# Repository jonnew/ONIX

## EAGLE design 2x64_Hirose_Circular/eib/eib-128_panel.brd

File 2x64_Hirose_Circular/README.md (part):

<!-- START doctoc generated TOC please keep comment here to allow auto update -->
<!-- DON'T EDIT THIS SECTION, INSTEAD RE-RUN doctoc TO UPDATE -->
**Table of Contents**  *generated with [DocToc](https://github.com/thlorenz/doctoc)*

- [128 channel headstage module for rat tetrode drives](#128-channel-headstage-module-for-rat-tetrode-drives)
  - [Features](#features)
  - [Bill of materials](#bill-of-materials)
  - [TODO](#todo)
  - [Hardware and Documentation Licensing](#hardware-and-documentation-licensing)

<!-- END doctoc generated TOC please keep comment here to allow auto update -->

### 128 channel headstage module for rat tetrode drives
A very low profile digital headstage for amplifying, filtering, and digitizing
microwire voltage data from a microdrive implant. Up to 256 wires (64 tetrodes)
can be acquired.

#### Features
- Circular form factor is aimed at conformation with **tetrode drive** assemblies
 - Low profile, stacked connectorization using 0.4mm pitch [Hirose DF40](http://www.digikey.com/product-search/en?FV=ffec4097) mezzanine headers
- SPI interface options for:
 - 128 channels using a single double data-rate LVDS bus (32 tetrodes)
 - 256 channels using two double data-rate LVDS busses (64 tetrodes)
- Integrated electrode plating and impedance testing

#### Bill of materials
The bill of materials for the headstage, EIBs, spacer boards, and SPI interface
boards can be found on [this google
doc](https://docs.google.com/spreadsheets/d/1F-KWcdvH_63iXjZf0cgCfDiFX6XXW3qw6rlR8DZrFpQ/edit?usp=sharing).

#### TODO
- [ ] For the implants with VTA recordings -- where will these static
  electrodes interface with the EIB. Will they just take an couple 'tetrode
  spots', or is something more specialized needed?
    - Edit: maybe make a special EIB with a connector coming from a flex pcb
      from the VTA implants.
- [ ] In talking to Jakob, I realized that I can share a single CS, MOSI, and
  SCLK bus among all 4 intan chips assuming (1) I don't mind that all the chips
  do the same thing (2) I make sure that the accumulating decrease in the
  effective resistance of having 2X100 ohm resistors close to each other
  (multidrop config) is not going to mess with the LVDS signal integrity.
    - To implement this (in the simplest way possible) I should just be able to
      jumper the CS, MOSI, and SCLK lines at the level of SPI interface board.
      If this works without chaning any of the headstage terminations, then
      great, I just saved 6 wires!
    - Note that this strategy does not require a change to the headstages, just
      the interface board. I will move forward with this idea because it will
      allow me to use the headstages for 128 channel acquisition in the
      meantime.
- [ ] Experiments with the color based tracker indicate that a diffuser,
  preferably something very similar to a tiny ping-pong ball is required on the
  head-direction LEDS on the SPI interface. In general, the SPI interface
  should accommodate whatever solution I come up with. Also, we can get rid of
  the 'wings' on the SPI interface since the geometric tracking idea was
  ill-conceived.
    - [ ] LED choices: Use green and blue for the SPI interface board. The orange
      LED matches the room lighting and is hard to track
- [ ] I need to make sure that he DF40 headers are not going to short onto the
  vias underneath the connectors on the EIB. This should be done empirically.
  - EDIT: they do not short, but there is a different problem: one of the gold
    pins on TT23 of the EIB hits the outer edge of the DF40 receptical above
    it. This pin needs to be moved. More generally, I need to add vertical
    keepouts to the DF40 parts to prevent this in the future.

#### Completed TODOs
- [x] Analog connections terminating at the inputs to an RHD chip do not need
  to feed through to the next board. However, digital connections __always__
  should feed through because they need to make it to the headstage interface
  - Is there a way to prevent stubs in the digital feed troughs that will go
    the wrong way?
- [x] Does it make a difference if the header or the receptacle is next to the
  RHD, specifically in regard to stack height. i.e. is there going to be enough
  room for the potted chip?
  - Selected a connector that has various options for stack height, up to 3mm
    which will be more than enough
- [x] Make sure the circuit has __ample test-points__, especially for probing
  GND, VDD, REF, ELEC_TEST, AUX_OUT.
  - I did my best, but was not able to get the ELEC_TEST pinned out due to
    routing issues. However, these signals have only a standard CMOS analog
    switch between their wire entry point and the RHD chip, so I'm not sure
    test points onboard are super critical.
- [x] Make the annualar ring on test points larger. Its hard to notice how tiny
  everything on these boards are when doing the layout.
- [x] Address Reid's concern about routing high impedance ELEC_TEST lines near
  digital signals
- [x] Add three axis accelerometer to one of the RHD's aux analog inputs
  - Ask for Reid's opinion on the possibility of this chip introducing HF noise
    into the RHD chip sitting right below it.
  - Reid did not think it would be an issue
- [x] Stack height concerns __test empirically using mockups__
 - The ADX is sitting right over an RHD. This leads to an effective stack
   height of their combined thickness. Solution: only populate the to ADX since
   thats all you need anyway. 
 - Just for the record, the ADX is 1.5 mm tall. The potted RHD is 0.8 mm. Total
   stack height = 2.3 + 2.3\*0.1 ~ 2.5 mm. This is a stack height option for
   the hirose connectors, so I think even if this issue arises for some reason,
   I can simply use a taller hirose.
 - The 74HC4053 is a pretty thick chip (standard TSSOP). I got 2 mm stack
   height headers. Will it fit? Its 1.75 mm thick max, so it should fit
   (barely). Also, need to take into account that the bottom headstage is
   rotated 90 deg. relative to the top. It looks like nothing will move
   underneath the 74HC4053 so long as the bottom ADX is not populated, but I
   need to test this on some cheapo boards before making the real ones!
 - Should get stack height of potted die from Reid just to be safe.
  - EDIT: Potted chip is ~0.8 mm tall. 
- [x] Do I really need the four holes in the center of the board. They are
  meant to be fore fiber optics, but they are a serious pain when routing the
  EIBs.
  - EDIT: ended up keeping them and taking the time to route around them
- [x] The EIB needs mounting holes. Maybe something that will fit the old style
  drive bodies with a triangular mounts.
 - Idea: Use a central t-nut on the drive body. This way, there only has to be
   one hole to mount the EIB and the connection will be very strong, especially
   if some sacrificial 'bumps' are placed on the 3D printed pad that will make
   contact with the bottom of the EIB.
 - I created a standard mounting fixture called EIB_MOUNT_A. This provides a
   center hole for a M2 or 2-56 screw and two alignment holes for tabs on the
   drive body's mounting plate.
- [x] The silkscreen on the tetrodes is too small. Make it bigger and move
  toward the inner part of the EIB.
- [x] On the SPI interface, on the mock ups from OSH park, small vias failed to
  support distinctions between octagon style plated holes and round holes. This
  means that my clever way of distinguish SPI interface polarity was a bust. 
- [x] The holes for the spi wire are too small - multiply by 1.5
- [x] The boarder silkscreens on the small passives (0402 and smaller) is too
  close to the pads and is not showing up on the boards.
- [x] Add VDD and GND test points, with large vias, to the periphery of the
  SPI interface board to make for easy testing using a benchtop power supply.
  In fact, do this for all the boards that don't have it already.
- [x] The SPI interface needs to be changed in the following ways.
  - Get rid of fins, they will never work
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
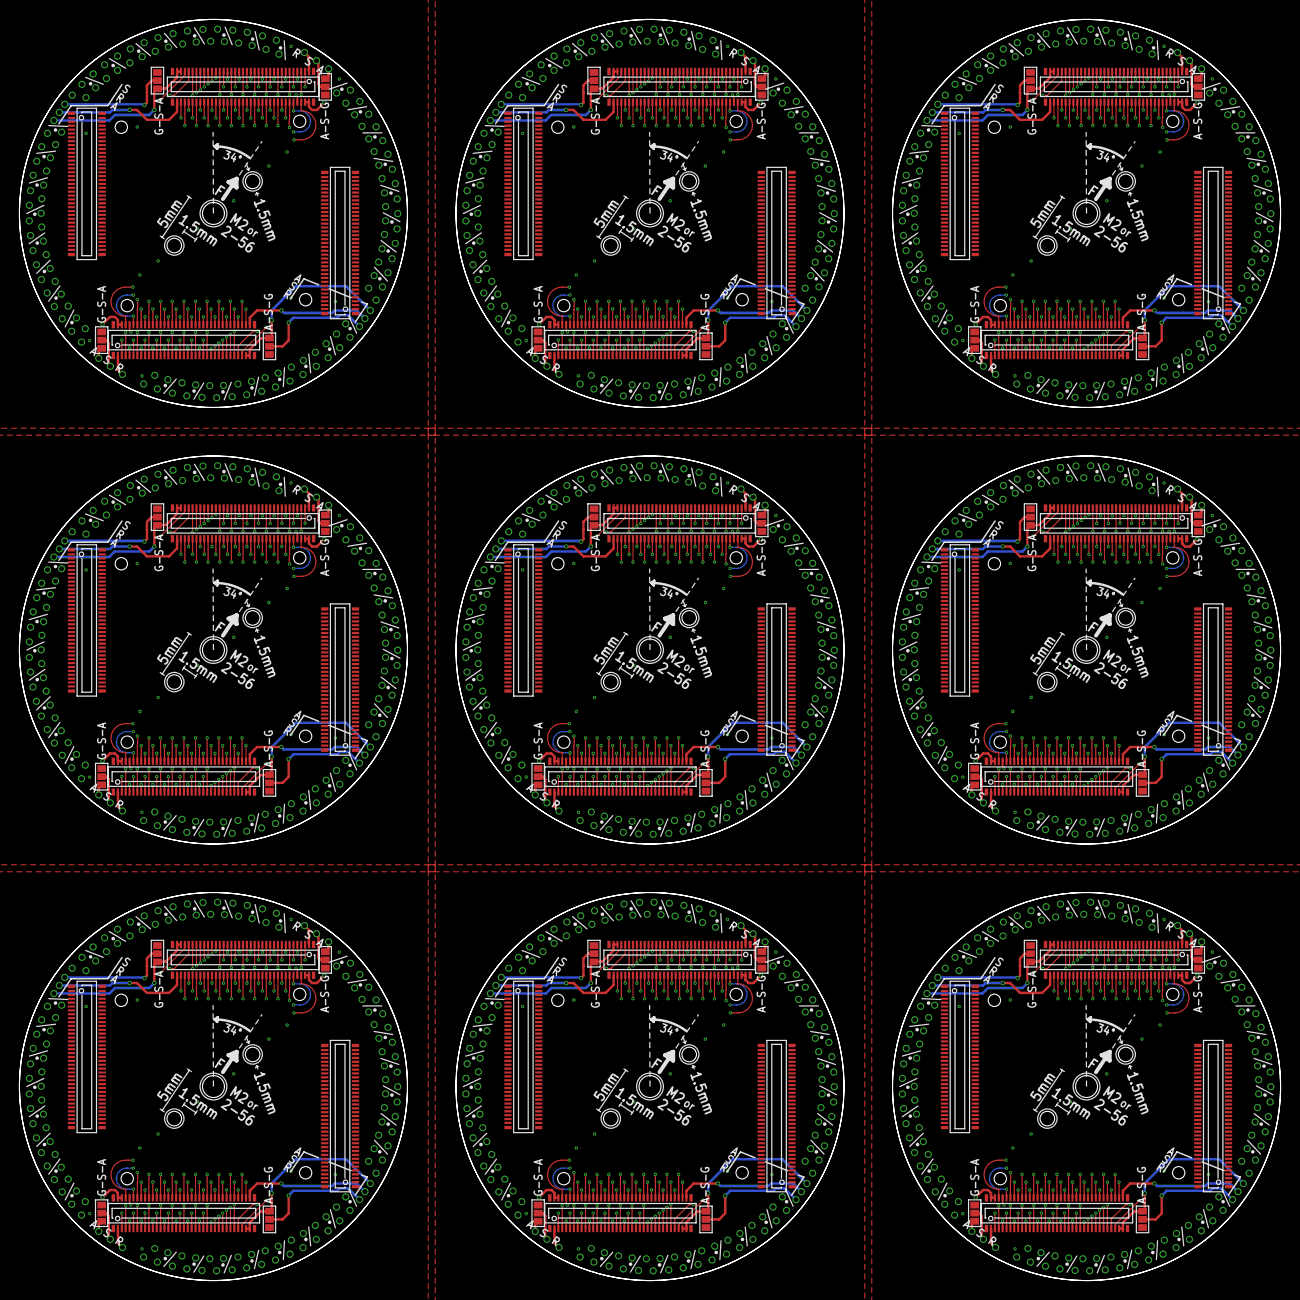
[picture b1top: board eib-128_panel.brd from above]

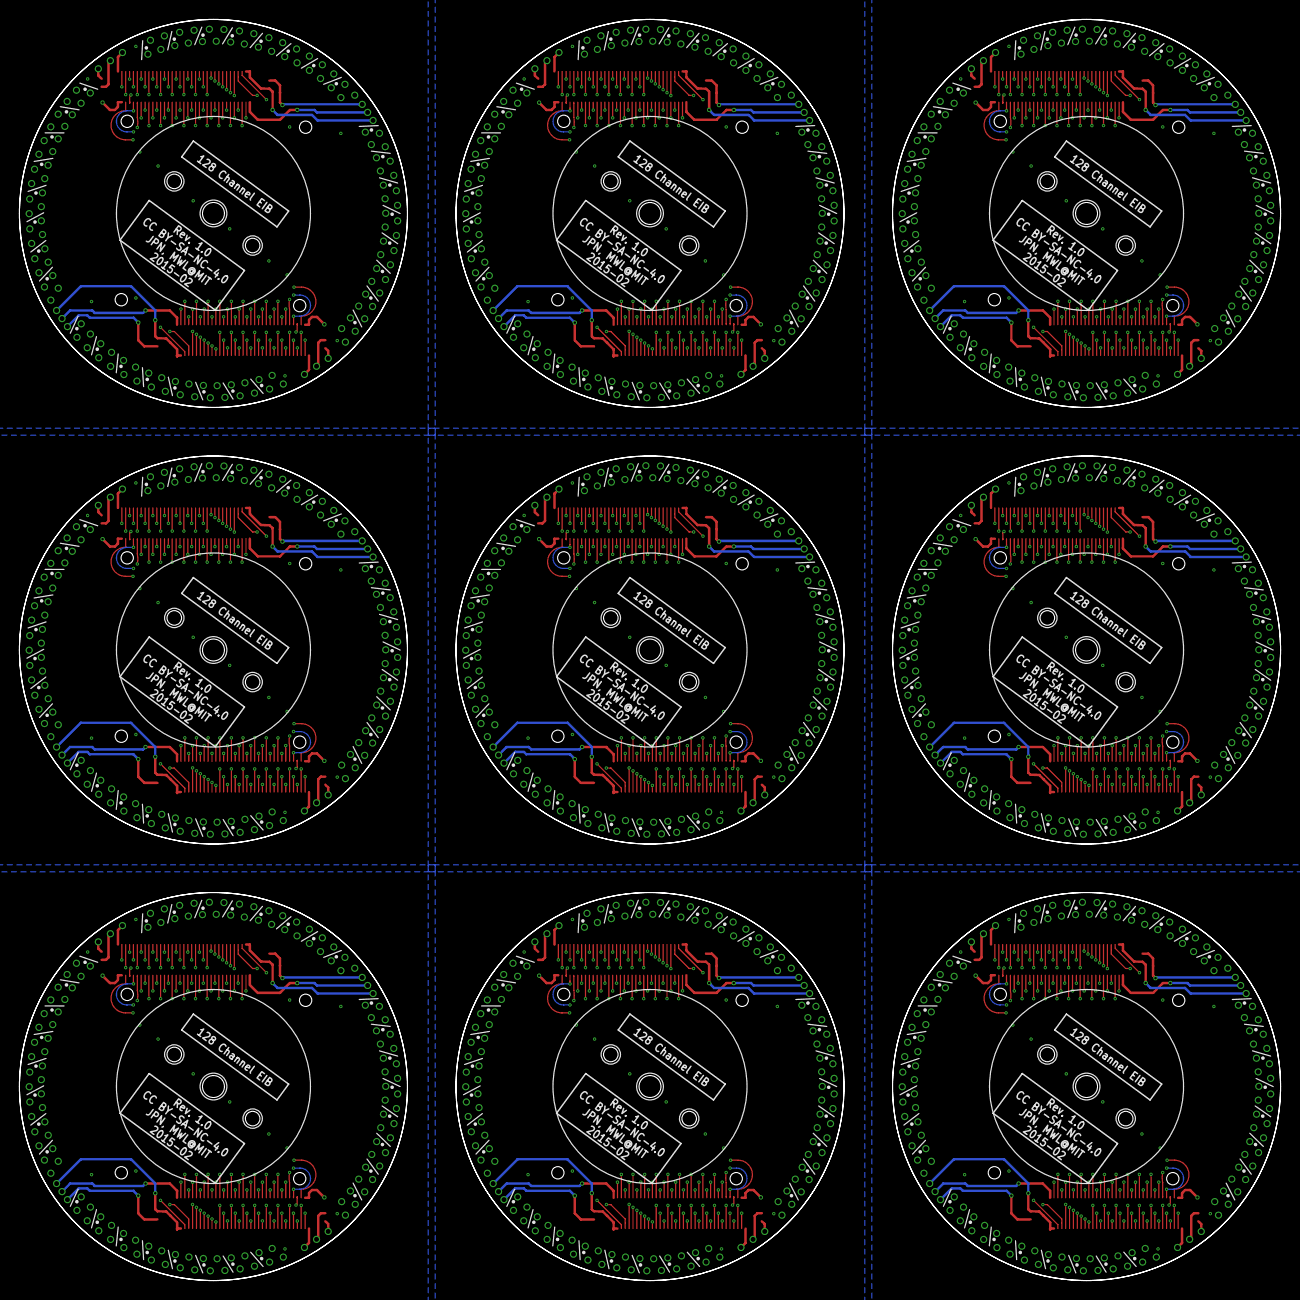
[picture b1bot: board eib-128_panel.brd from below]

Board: 4 copper layers, 130.0 x 130.0 mm, 477 parts (144 on the bottom side), 1269 nets.

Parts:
AGND_A0, AGND_A1, AGND_A2, AGND_A3, AGND_A4, AGND_A5, AGND_A6, AGND_A7, AGND_A8, AGND_A9, AGND_A10, AGND_A11, AGND_A12, AGND_A13, AGND_A14, AGND_A15, AGND_A16, AGND_A17: LRG_GP; GOLDPIN_0.5ID_0.7OD
AGND_B0, AGND_B1, AGND_B2, AGND_B3, AGND_B4, AGND_B5, AGND_B6, AGND_B7, AGND_B8, AGND_B9, AGND_B10, AGND_B11, AGND_B12, AGND_B13, AGND_B14, AGND_B15, AGND_B16, AGND_B17: LRG_GP; GOLDPIN_0.5ID_0.7OD
AIN_N0T, AIN_N0T1, AIN_N0T2, AIN_N0T3, AIN_N0T4, AIN_N0T5, AIN_N0T6, AIN_N0T7, AIN_N0T8: DF40HEAD; DF40-70HEAD-EIB
AIN_S0T, AIN_S0T1, AIN_S0T2, AIN_S0T3, AIN_S0T4, AIN_S0T5, AIN_S0T6, AIN_S0T7, AIN_S0T8: DF40HEAD; DF40-70HEAD-EIB
MECH_E0T, MECH_E0T1, MECH_E0T2, MECH_E0T3, MECH_E0T4, MECH_E0T5, MECH_E0T6, MECH_E0T7, MECH_E0T8: DF40HEAD; DF40-70HEAD
MECH_W0T, MECH_W0T1, MECH_W0T2, MECH_W0T3, MECH_W0T4, MECH_W0T5, MECH_W0T6, MECH_W0T7, MECH_W0T8: DF40HEAD; DF40-70HEAD
REF_A0, REF_A1, REF_A2, REF_A3, REF_A4, REF_A5, REF_A6, REF_A7, REF_A8, REF_A9, REF_A10, REF_A11, REF_A12, REF_A13, REF_A14, REF_A15, REF_A16, REF_A17: LRG_GP; GOLDPIN_0.5ID_0.7OD
REF_B0, REF_B1, REF_B2, REF_B3, REF_B4, REF_B5, REF_B6, REF_B7, REF_B8, REF_B9, REF_B10, REF_B11, REF_B12, REF_B13, REF_B14, REF_B15, REF_B16, REF_B17: LRG_GP; GOLDPIN_0.5ID_0.7OD
SHLD_A0, SHLD_A1, SHLD_A2, SHLD_A3, SHLD_A4, SHLD_A5, SHLD_A6, SHLD_A7, SHLD_A8, SHLD_A9, SHLD_A10, SHLD_A11, SHLD_A12, SHLD_A13, SHLD_A14, SHLD_A15, SHLD_A16, SHLD_A17: LRG_GP; GOLDPIN_0.5ID_0.7OD
SHLD_B0, SHLD_B1, SHLD_B2, SHLD_B3, SHLD_B4, SHLD_B5, SHLD_B6, SHLD_B7, SHLD_B8, SHLD_B9, SHLD_B10, SHLD_B11, SHLD_B12, SHLD_B13, SHLD_B14, SHLD_B15, SHLD_B16, SHLD_B17: LRG_GP; GOLDPIN_0.5ID_0.7OD
SJ_A0, SJ_A1, SJ_A2, SJ_A3, SJ_A4, SJ_A5, SJ_A6, SJ_A7, SJ_A8, SJ_A9, SJ_A10, SJ_A11, SJ_A12, SJ_A13, SJ_A14, SJ_A15, SJ_A16, SJ_A17: SJ_2_0402
SJ_B0, SJ_B1, SJ_B2, SJ_B3, SJ_B4, SJ_B5, SJ_B6, SJ_B7, SJ_B8, SJ_B9, SJ_B10, SJ_B11, SJ_B12, SJ_B13, SJ_B14, SJ_B15, SJ_B16, SJ_B17: SJ_2_0402
TET0, TET32, TET64, TET96, TET128, TET160, TET192, TET224, TET256: 0; TETRODE_128_0.5ID_0.7OD
TET1, TET33, TET65, TET97, TET129, TET161, TET193, TET225, TET257: 1; TETRODE_128_0.5ID_0.7OD
TET2, TET34, TET66, TET98, TET130, TET162, TET194, TET226, TET258: 2; TETRODE_128_0.5ID_0.7OD
TET3, TET35, TET67, TET99, TET131, TET163, TET195, TET227, TET259: 3; TETRODE_128_0.5ID_0.7OD
TET4, TET36, TET68, TET100, TET132, TET164, TET196, TET228, TET260: 4; TETRODE_128_0.5ID_0.7OD
TET5, TET37, TET69, TET101, TET133, TET165, TET197, TET229, TET261: 5; TETRODE_128_0.5ID_0.7OD
TET6, TET38, TET70, TET102, TET134, TET166, TET198, TET230, TET262: 6; TETRODE_128_0.5ID_0.7OD
TET7, TET39, TET71, TET103, TET135, TET167, TET199, TET231, TET263: 7; TETRODE_128_0.5ID_0.7OD
TET8, TET40, TET72, TET104, TET136, TET168, TET200, TET232, TET264: 8; TETRODE_128_0.5ID_0.7OD
TET9, TET41, TET73, TET105, TET137, TET169, TET201, TET233, TET265: 9; TETRODE_128_0.5ID_0.7OD
TET10, TET42, TET74, TET106, TET138, TET170, TET202, TET234, TET266: 10; TETRODE_128_0.5ID_0.7OD
TET11, TET43, TET75, TET107, TET139, TET171, TET203, TET235, TET267: 11; TETRODE_128_0.5ID_0.7OD
TET12, TET44, TET76, TET108, TET140, TET172, TET204, TET236, TET268: 12; TETRODE_128_0.5ID_0.7OD
TET13, TET45, TET77, TET109, TET141, TET173, TET205, TET237, TET269: 13; TETRODE_128_0.5ID_0.7OD
TET14, TET46, TET78, TET110, TET142, TET174, TET206, TET238, TET270: 14; TETRODE_128_0.5ID_0.7OD
TET15, TET47, TET79, TET111, TET143, TET175, TET207, TET239, TET271: 15; TETRODE_128_0.5ID_0.7OD
TET16, TET48, TET80, TET112, TET144, TET176, TET208, TET240, TET272: 16; TETRODE_128_0.5ID_0.7OD
TET17, TET49, TET81, TET113, TET145, TET177, TET209, TET241, TET273: 17; TETRODE_128_0.5ID_0.7OD
TET18, TET50, TET82, TET114, TET146, TET178, TET210, TET242, TET274: 18; TETRODE_128_0.5ID_0.7OD
TET19, TET51, TET83, TET115, TET147, TET179, TET211, TET243, TET275: 19; TETRODE_128_0.5ID_0.7OD
TET20, TET52, TET84, TET116, TET148, TET180, TET212, TET244, TET276: 20; TETRODE_128_0.5ID_0.7OD
TET21, TET53, TET85, TET117, TET149, TET181, TET213, TET245, TET277: 21; TETRODE_128_0.5ID_0.7OD
TET22, TET54, TET86, TET118, TET150, TET182, TET214, TET246, TET278: 22; TETRODE_128_0.5ID_0.7OD
TET23, TET55, TET87, TET119, TET151, TET183, TET215, TET247, TET279: 23; TETRODE_128_0.5ID_0.7OD
TET24, TET56, TET88, TET120, TET152, TET184, TET216, TET248, TET280: 24; TETRODE_128_0.5ID_0.7OD
TET25, TET57, TET89, TET121, TET153, TET185, TET217, TET249, TET281: 25; TETRODE_128_0.5ID_0.7OD
TET26, TET58, TET90, TET122, TET154, TET186, TET218, TET250, TET282: 26; TETRODE_128_0.5ID_0.7OD
TET27, TET59, TET91, TET123, TET155, TET187, TET219, TET251, TET283: 27; TETRODE_128_0.5ID_0.7OD
TET28, TET60, TET92, TET124, TET156, TET188, TET220, TET252, TET284: 28; TETRODE_128_0.5ID_0.7OD
TET29, TET61, TET93, TET125, TET157, TET189, TET221, TET253, TET285: 29; TETRODE_128_0.5ID_0.7OD
TET30, TET62, TET94, TET126, TET158, TET190, TET222, TET254, TET286: 30; TETRODE_128_0.5ID_0.7OD
TET31, TET63, TET95, TET127, TET159, TET191, TET223, TET255, TET287: 31; TETRODE_128_0.5ID_0.7OD
U$1, U$2, U$3, U$4, U$5, U$6, U$7, U$8, U$9: EIB_MOUNT_A

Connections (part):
AGND_A0: AGND_A0.P$1, AIN_N0T.69, AIN_N0T.70, SJ_A0.2
AGND_A1: AGND_A1.P$1, AIN_N0T.34, AIN_N0T.35, SJ_A1.2
AGND_A2: AGND_A3.P$1, AIN_N0T1.69, AIN_N0T1.70, SJ_A2.2
AGND_A3: AGND_A2.P$1, AIN_N0T1.34, AIN_N0T1.35, SJ_A3.2
AGND_A4: AGND_A5.P$1, AIN_N0T2.69, AIN_N0T2.70, SJ_A4.2
AGND_A5: AGND_A4.P$1, AIN_N0T2.34, AIN_N0T2.35, SJ_A5.2
AGND_A6: AGND_A7.P$1, AIN_N0T3.69, AIN_N0T3.70, SJ_A6.2
AGND_A7: AGND_A6.P$1, AIN_N0T3.34, AIN_N0T3.35, SJ_A7.2
AGND_A8: AGND_A9.P$1, AIN_N0T4.69, AIN_N0T4.70, SJ_A8.2
AGND_A9: AGND_A8.P$1, AIN_N0T4.34, AIN_N0T4.35, SJ_A9.2
AGND_A10: AGND_A11.P$1, AIN_N0T5.69, AIN_N0T5.70, SJ_A10.2
AGND_A11: AGND_A10.P$1, AIN_N0T5.34, AIN_N0T5.35, SJ_A11.2
AGND_A12: AGND_A13.P$1, AIN_N0T6.69, AIN_N0T6.70, SJ_A12.2
AGND_A13: AGND_A12.P$1, AIN_N0T6.34, AIN_N0T6.35, SJ_A13.2
AGND_A14: AGND_A15.P$1, AIN_N0T7.69, AIN_N0T7.70, SJ_A14.2
AGND_A15: AGND_A14.P$1, AIN_N0T7.34, AIN_N0T7.35, SJ_A15.2
AGND_A16: AGND_A17.P$1, AIN_N0T8.69, AIN_N0T8.70, SJ_A16.2
AGND_A17: AGND_A16.P$1, AIN_N0T8.34, AIN_N0T8.35, SJ_A17.2
AGND_B0: AGND_B0.P$1, AIN_S0T.69, AIN_S0T.70, SJ_B0.2
AGND_B1: AGND_B1.P$1, AIN_S0T.34, AIN_S0T.35, SJ_B1.2
AGND_B2: AGND_B3.P$1, AIN_S0T1.34, AIN_S0T1.35, SJ_B3.2
AGND_B3: AGND_B2.P$1, AIN_S0T1.69, AIN_S0T1.70, SJ_B2.2
AGND_B4: AGND_B5.P$1, AIN_S0T2.34, AIN_S0T2.35, SJ_B5.2
AGND_B5: AGND_B4.P$1, AIN_S0T2.69, AIN_S0T2.70, SJ_B4.2
AGND_B6: AGND_B7.P$1, AIN_S0T3.34, AIN_S0T3.35, SJ_B7.2
AGND_B7: AGND_B6.P$1, AIN_S0T3.69, AIN_S0T3.70, SJ_B6.2
AGND_B8: AGND_B9.P$1, AIN_S0T4.34, AIN_S0T4.35, SJ_B9.2
AGND_B9: AGND_B8.P$1, AIN_S0T4.69, AIN_S0T4.70, SJ_B8.2
AGND_B10: AGND_B11.P$1, AIN_S0T5.34, AIN_S0T5.35, SJ_B11.2
AGND_B11: AGND_B10.P$1, AIN_S0T5.69, AIN_S0T5.70, SJ_B10.2
AGND_B12: AGND_B13.P$1, AIN_S0T6.34, AIN_S0T6.35, SJ_B13.2
AGND_B13: AGND_B12.P$1, AIN_S0T6.69, AIN_S0T6.70, SJ_B12.2
AGND_B14: AGND_B15.P$1, AIN_S0T7.34, AIN_S0T7.35, SJ_B15.2
AGND_B15: AGND_B14.P$1, AIN_S0T7.69, AIN_S0T7.70, SJ_B14.2
AGND_B16: AGND_B17.P$1, AIN_S0T8.34, AIN_S0T8.35, SJ_B17.2
AGND_B17: AGND_B16.P$1, AIN_S0T8.69, AIN_S0T8.70, SJ_B16.2
GND: SJ_A0.1, SJ_A1.1, SJ_B0.1, SJ_B1.1
GND1: SJ_A2.1, SJ_A3.1, SJ_B2.1, SJ_B3.1
GND2: SJ_A4.1, SJ_A5.1, SJ_B4.1, SJ_B5.1
GND3: SJ_A6.1, SJ_A7.1, SJ_B6.1, SJ_B7.1
GND4: SJ_A8.1, SJ_A9.1, SJ_B8.1, SJ_B9.1
GND5: SJ_A10.1, SJ_A11.1, SJ_B10.1, SJ_B11.1
GND6: SJ_A12.1, SJ_A13.1, SJ_B12.1, SJ_B13.1
GND7: SJ_A14.1, SJ_A15.1, SJ_B14.1, SJ_B15.1
GND8: SJ_A16.1, SJ_A17.1, SJ_B16.1, SJ_B17.1
unnamed: SHLD_A0.P$1, SJ_A0.COM
unnamed: SHLD_A1.P$1, SJ_A1.COM
unnamed: SHLD_B0.P$1, SJ_B0.COM
unnamed: SHLD_B1.P$1, SJ_B1.COM
unnamed: AIN_N0T1.33, TET39.3
unnamed: AIN_N0T1.32, TET39.2
unnamed: AIN_N0T1.31, AIN_N0T1.P31, TET39.1
unnamed: AIN_N0T1.30, AIN_N0T1.P30, TET39.0
unnamed: AIN_N0T1.29, AIN_N0T1.P29, TET38.3
unnamed: AIN_N0T1.28, AIN_N0T1.P28, TET38.2
unnamed: AIN_N0T1.27, AIN_N0T1.P27, TET38.1
unnamed: AIN_N0T1.26, AIN_N0T1.P26, TET38.0
unnamed: AIN_N0T1.25, AIN_N0T1.P25, TET37.3
unnamed: AIN_N0T1.24, AIN_N0T1.P24, TET37.2
unnamed: AIN_N0T1.23, AIN_N0T1.P23, TET37.1
unnamed: AIN_N0T1.22, AIN_N0T1.P22, TET37.0
unnamed: AIN_N0T1.21, AIN_N0T1.P21, TET36.3
unnamed: AIN_N0T1.20, AIN_N0T1.P20, TET36.2
unnamed: AIN_N0T1.19, AIN_N0T1.P19, TET36.1
unnamed: AIN_N0T1.18, AIN_N0T1.P18, TET36.0
unnamed: AIN_N0T1.17, AIN_N0T1.P17, TET35.3
unnamed: AIN_N0T1.16, AIN_N0T1.P16, TET35.2
unnamed: AIN_N0T1.15, AIN_N0T1.P15, TET35.1
unnamed: AIN_N0T1.14, AIN_N0T1.P14, TET35.0
unnamed: AIN_N0T1.13, AIN_N0T1.P13, TET34.3
unnamed: AIN_N0T1.12, AIN_N0T1.P12, TET34.2
unnamed: AIN_N0T1.11, AIN_N0T1.P11, TET34.1
unnamed: AIN_N0T1.10, AIN_N0T1.P10, TET34.0
unnamed: AIN_N0T1.9, AIN_N0T1.P9, TET33.3
unnamed: AIN_N0T1.8, AIN_N0T1.P8, TET33.2
unnamed: AIN_N0T1.7, AIN_N0T1.P7, TET33.1
unnamed: AIN_N0T1.6, AIN_N0T1.P6, TET33.0
unnamed: AIN_N0T1.5, AIN_N0T1.P5, TET32.3
unnamed: AIN_N0T1.4, AIN_N0T1.P4, TET32.2
unnamed: AIN_N0T1.3, AIN_N0T1.P3, TET32.1
unnamed: AIN_N0T1.38, AIN_N0T1.P38, TET40.1
unnamed: AIN_N0T1.39, AIN_N0T1.P39, TET40.2
unnamed: AIN_N0T1.40, AIN_N0T1.P40, TET40.3
unnamed: AIN_N0T1.41, AIN_N0T1.P41, TET41.0
unnamed: AIN_N0T1.42, AIN_N0T1.P42, TET41.1
unnamed: AIN_N0T1.43, AIN_N0T1.P43, TET41.2
unnamed: AIN_N0T1.44, AIN_N0T1.P44, TET41.3
unnamed: AIN_N0T1.45, AIN_N0T1.P45, TET42.0
unnamed: AIN_N0T1.46, AIN_N0T1.P46, TET42.1
unnamed: AIN_N0T1.47, AIN_N0T1.P47, TET42.2
unnamed: AIN_N0T1.48, AIN_N0T1.P48, TET42.3
unnamed: AIN_N0T1.49, AIN_N0T1.P49, TET43.0
unnamed: AIN_N0T1.50, AIN_N0T1.P50, TET43.1
unnamed: AIN_N0T1.51, AIN_N0T1.P51, TET43.2
unnamed: AIN_N0T1.52, AIN_N0T1.P52, TET43.3
unnamed: AIN_N0T1.53, AIN_N0T1.P53, TET44.0
unnamed: AIN_N0T1.54, AIN_N0T1.P54, TET44.1
unnamed: AIN_N0T1.55, AIN_N0T1.P55, TET44.2
unnamed: AIN_N0T1.56, AIN_N0T1.P56, TET44.3
unnamed: AIN_N0T1.57, AIN_N0T1.P57, TET45.0
unnamed: AIN_N0T1.58, AIN_N0T1.P58, TET45.1
unnamed: AIN_N0T1.59, AIN_N0T1.P59, TET45.2
unnamed: AIN_N0T1.60, AIN_N0T1.P60, TET45.3
unnamed: AIN_N0T1.61, AIN_N0T1.P61, TET46.0
unnamed: AIN_N0T1.62, AIN_N0T1.P62, TET46.1
unnamed: AIN_N0T1.63, AIN_N0T1.P63, TET46.2
unnamed: AIN_N0T1.64, AIN_N0T1.P64, TET46.3
unnamed: AIN_N0T1.65, TET47.0
unnamed: AIN_N0T1.66, TET47.1
unnamed: AIN_S0T.33, TET23.0
unnamed: AIN_S0T.32, TET23.1
unnamed: AIN_S0T.31, AIN_S0T.P31, TET23.2
unnamed: AIN_S0T.30, AIN_S0T.P30, TET23.3
unnamed: AIN_S0T.29, AIN_S0T.P29, TET22.0
unnamed: AIN_S0T.28, AIN_S0T.P28, TET22.1
unnamed: AIN_S0T.27, AIN_S0T.P27, TET22.2
unnamed: AIN_S0T.26, AIN_S0T.P26, TET22.3
unnamed: AIN_S0T.25, AIN_S0T.P25, TET21.0
unnamed: AIN_S0T.24, AIN_S0T.P24, TET21.1
unnamed: AIN_S0T.23, AIN_S0T.P23, TET21.2
unnamed: AIN_S0T.22, AIN_S0T.P22, TET21.3
unnamed: AIN_S0T.21, AIN_S0T.P21, TET20.0
unnamed: AIN_S0T.20, AIN_S0T.P20, TET20.1
unnamed: AIN_S0T.19, AIN_S0T.P19, TET20.2
unnamed: AIN_S0T.18, AIN_S0T.P18, TET20.3
unnamed: AIN_S0T.17, AIN_S0T.P17, TET19.0
unnamed: AIN_S0T.16, AIN_S0T.P16, TET19.1
unnamed: AIN_S0T.15, AIN_S0T.P15, TET19.2
unnamed: AIN_S0T.14, AIN_S0T.P14, TET19.3
unnamed: AIN_S0T.13, AIN_S0T.P13, TET18.0
unnamed: AIN_S0T.12, AIN_S0T.P12, TET18.1
unnamed: AIN_S0T.11, AIN_S0T.P11, TET18.2
unnamed: AIN_S0T.10, AIN_S0T.P10, TET18.3
unnamed: AIN_S0T.9, AIN_S0T.P9, TET17.0
unnamed: AIN_S0T.8, AIN_S0T.P8, TET17.1
unnamed: AIN_S0T.7, AIN_S0T.P7, TET17.2
unnamed: AIN_S0T.6, AIN_S0T.P6, TET17.3
unnamed: AIN_S0T.5, AIN_S0T.P5, TET16.0
unnamed: AIN_S0T.4, AIN_S0T.P4, TET16.1
unnamed: AIN_S0T.3, AIN_S0T.P3, TET16.2
unnamed: AIN_S0T.38, AIN_S0T.P38, TET24.2
unnamed: AIN_S0T.39, AIN_S0T.P39, TET24.1
unnamed: AIN_S0T.40, AIN_S0T.P40, TET24.0
unnamed: AIN_S0T.41, AIN_S0T.P41, TET25.3
unnamed: AIN_S0T.42, AIN_S0T.P42, TET25.2
unnamed: AIN_S0T.43, AIN_S0T.P43, TET25.1
unnamed: AIN_S0T.44, AIN_S0T.P44, TET25.0
unnamed: AIN_S0T.45, AIN_S0T.P45, TET26.3
unnamed: AIN_S0T.46, AIN_S0T.P46, TET26.2
unnamed: AIN_S0T.47, AIN_S0T.P47, TET26.1
unnamed: AIN_S0T.48, AIN_S0T.P48, TET26.0
unnamed: AIN_S0T.49, AIN_S0T.P49, TET27.3
unnamed: AIN_S0T.50, AIN_S0T.P50, TET27.2
unnamed: AIN_S0T.51, AIN_S0T.P51, TET27.1
unnamed: AIN_S0T.52, AIN_S0T.P52, TET27.0
unnamed: AIN_S0T.53, AIN_S0T.P53, TET28.3
unnamed: AIN_S0T.54, AIN_S0T.P54, TET28.2
unnamed: AIN_S0T.55, AIN_S0T.P55, TET28.1
unnamed: AIN_S0T.56, AIN_S0T.P56, TET28.0
unnamed: AIN_S0T.57, AIN_S0T.P57, TET29.3
unnamed: AIN_S0T.58, AIN_S0T.P58, TET29.2
unnamed: AIN_S0T.59, AIN_S0T.P59, TET29.1
unnamed: AIN_S0T.60, AIN_S0T.P60, TET29.0
unnamed: AIN_S0T.61, AIN_S0T.P61, TET30.3
unnamed: AIN_S0T.62, AIN_S0T.P62, TET30.2
unnamed: AIN_S0T.63, AIN_S0T.P63, TET30.1
unnamed: AIN_S0T.64, AIN_S0T.P64, TET30.0
unnamed: AIN_S0T.65, TET31.3
unnamed: AIN_S0T.66, TET31.2
unnamed: AIN_S0T.67, TET31.1
unnamed: AIN_S0T.68, TET31.0
unnamed: AIN_S0T.2, AIN_S0T.P2, TET16.3
unnamed: AIN_S0T.37, AIN_S0T.P37, TET24.3
unnamed: AIN_N0T1.67, TET47.2
unnamed: AIN_N0T1.68, TET47.3
unnamed: AIN_N0T1.2, AIN_N0T1.P2, TET32.0
unnamed: AIN_N0T1.37, AIN_N0T1.P37, TET40.0
unnamed: AIN_S0T1.33, TET55.0
unnamed: AIN_S0T1.32, TET55.1
unnamed: AIN_S0T1.31, AIN_S0T1.P31, TET55.2
unnamed: AIN_S0T1.30, AIN_S0T1.P30, TET55.3
unnamed: AIN_S0T1.29, AIN_S0T1.P29, TET54.0
unnamed: AIN_S0T1.28, AIN_S0T1.P28, TET54.1
unnamed: AIN_S0T1.27, AIN_S0T1.P27, TET54.2
unnamed: AIN_S0T1.26, AIN_S0T1.P26, TET54.3
unnamed: AIN_S0T1.25, AIN_S0T1.P25, TET53.0
unnamed: AIN_S0T1.24, AIN_S0T1.P24, TET53.1
unnamed: AIN_S0T1.23, AIN_S0T1.P23, TET53.2
unnamed: AIN_S0T1.22, AIN_S0T1.P22, TET53.3
unnamed: AIN_S0T1.21, AIN_S0T1.P21, TET52.0
unnamed: AIN_S0T1.20, AIN_S0T1.P20, TET52.1
unnamed: AIN_S0T1.19, AIN_S0T1.P19, TET52.2
unnamed: AIN_S0T1.18, AIN_S0T1.P18, TET52.3
unnamed: AIN_S0T1.17, AIN_S0T1.P17, TET51.0
unnamed: AIN_S0T1.16, AIN_S0T1.P16, TET51.1
unnamed: AIN_S0T1.15, AIN_S0T1.P15, TET51.2
unnamed: AIN_S0T1.14, AIN_S0T1.P14, TET51.3
unnamed: AIN_S0T1.13, AIN_S0T1.P13, TET50.0
unnamed: AIN_S0T1.12, AIN_S0T1.P12, TET50.1
unnamed: AIN_S0T1.11, AIN_S0T1.P11, TET50.2
unnamed: AIN_S0T1.10, AIN_S0T1.P10, TET50.3
unnamed: AIN_S0T1.9, AIN_S0T1.P9, TET49.0
unnamed: AIN_S0T1.8, AIN_S0T1.P8, TET49.1
unnamed: AIN_S0T1.7, AIN_S0T1.P7, TET49.2
unnamed: AIN_S0T1.6, AIN_S0T1.P6, TET49.3
unnamed: AIN_S0T1.5, AIN_S0T1.P5, TET48.0
unnamed: AIN_S0T1.4, AIN_S0T1.P4, TET48.1
unnamed: AIN_S0T1.3, AIN_S0T1.P3, TET48.2
unnamed: AIN_S0T1.38, AIN_S0T1.P38, TET56.2
unnamed: AIN_S0T1.39, AIN_S0T1.P39, TET56.1
unnamed: AIN_S0T1.40, AIN_S0T1.P40, TET56.0
unnamed: AIN_S0T1.41, AIN_S0T1.P41, TET57.3
unnamed: AIN_S0T1.42, AIN_S0T1.P42, TET57.2
unnamed: AIN_S0T1.43, AIN_S0T1.P43, TET57.1
unnamed: AIN_S0T1.44, AIN_S0T1.P44, TET57.0
unnamed: AIN_S0T1.45, AIN_S0T1.P45, TET58.3
unnamed: AIN_S0T1.46, AIN_S0T1.P46, TET58.2
unnamed: AIN_S0T1.47, AIN_S0T1.P47, TET58.1
unnamed: AIN_S0T1.48, AIN_S0T1.P48, TET58.0
unnamed: AIN_S0T1.49, AIN_S0T1.P49, TET59.3
unnamed: AIN_S0T1.50, AIN_S0T1.P50, TET59.2
unnamed: AIN_S0T1.51, AIN_S0T1.P51, TET59.1
unnamed: AIN_S0T1.52, AIN_S0T1.P52, TET59.0
unnamed: AIN_S0T1.53, AIN_S0T1.P53, TET60.3
unnamed: AIN_S0T1.54, AIN_S0T1.P54, TET60.2
unnamed: AIN_S0T1.55, AIN_S0T1.P55, TET60.1
unnamed: AIN_S0T1.56, AIN_S0T1.P56, TET60.0
unnamed: AIN_S0T1.57, AIN_S0T1.P57, TET61.3
unnamed: AIN_S0T1.58, AIN_S0T1.P58, TET61.2
unnamed: AIN_S0T1.59, AIN_S0T1.P59, TET61.1
unnamed: AIN_S0T1.60, AIN_S0T1.P60, TET61.0
unnamed: AIN_S0T1.61, AIN_S0T1.P61, TET62.3
unnamed: AIN_S0T1.62, AIN_S0T1.P62, TET62.2
unnamed: AIN_S0T1.63, AIN_S0T1.P63, TET62.1
unnamed: AIN_S0T1.64, AIN_S0T1.P64, TET62.0
unnamed: AIN_S0T1.65, TET63.3
unnamed: AIN_S0T1.66, TET63.2
unnamed: AIN_S0T1.67, TET63.1
unnamed: AIN_S0T1.68, TET63.0
unnamed: AIN_S0T1.2, AIN_S0T1.P2, TET48.3
unnamed: AIN_S0T1.37, AIN_S0T1.P37, TET56.3
unnamed: SHLD_A2.P$1, SJ_A2.COM
unnamed: SHLD_A3.P$1, SJ_A3.COM
unnamed: AIN_N0T.33, TET7.3
unnamed: AIN_N0T.32, TET7.2
unnamed: AIN_N0T.31, AIN_N0T.P31, TET7.1
unnamed: AIN_N0T.30, AIN_N0T.P30, TET7.0
unnamed: AIN_N0T.29, AIN_N0T.P29, TET6.3
unnamed: AIN_N0T.28, AIN_N0T.P28, TET6.2
unnamed: AIN_N0T.27, AIN_N0T.P27, TET6.1
unnamed: AIN_N0T.26, AIN_N0T.P26, TET6.0
unnamed: AIN_N0T.25, AIN_N0T.P25, TET5.3
unnamed: AIN_N0T.24, AIN_N0T.P24, TET5.2
unnamed: AIN_N0T.23, AIN_N0T.P23, TET5.1
unnamed: AIN_N0T.22, AIN_N0T.P22, TET5.0
unnamed: AIN_N0T.21, AIN_N0T.P21, TET4.3
unnamed: AIN_N0T.20, AIN_N0T.P20, TET4.2
unnamed: AIN_N0T.19, AIN_N0T.P19, TET4.1
unnamed: AIN_N0T.18, AIN_N0T.P18, TET4.0
unnamed: AIN_N0T.17, AIN_N0T.P17, TET3.3
unnamed: AIN_N0T.16, AIN_N0T.P16, TET3.2
unnamed: AIN_N0T.15, AIN_N0T.P15, TET3.1
unnamed: AIN_N0T.14, AIN_N0T.P14, TET3.0
unnamed: AIN_N0T.13, AIN_N0T.P13, TET2.3
unnamed: AIN_N0T.12, AIN_N0T.P12, TET2.2
unnamed: AIN_N0T.11, AIN_N0T.P11, TET2.1
unnamed: AIN_N0T.10, AIN_N0T.P10, TET2.0
unnamed: AIN_N0T.9, AIN_N0T.P9, TET1.3
unnamed: AIN_N0T.8, AIN_N0T.P8, TET1.2
unnamed: AIN_N0T.7, AIN_N0T.P7, TET1.1
unnamed: AIN_N0T.6, AIN_N0T.P6, TET1.0
unnamed: AIN_N0T.5, AIN_N0T.P5, TET0.3
unnamed: AIN_N0T.4, AIN_N0T.P4, TET0.2
unnamed: AIN_N0T.3, AIN_N0T.P3, TET0.1
unnamed: AIN_N0T.2, AIN_N0T.P2, TET0.0
unnamed: AIN_N0T.38, AIN_N0T.P38, TET8.1
unnamed: AIN_N0T.39, AIN_N0T.P39, TET8.2
unnamed: AIN_N0T.40, AIN_N0T.P40, TET8.3
unnamed: AIN_N0T.41, AIN_N0T.P41, TET9.0
unnamed: AIN_N0T.42, AIN_N0T.P42, TET9.1
unnamed: AIN_N0T.43, AIN_N0T.P43, TET9.2
unnamed: AIN_N0T.44, AIN_N0T.P44, TET9.3
unnamed: AIN_N0T.45, AIN_N0T.P45, TET10.0
unnamed: AIN_N0T.46, AIN_N0T.P46, TET10.1
unnamed: AIN_N0T.47, AIN_N0T.P47, TET10.2
unnamed: AIN_N0T.48, AIN_N0T.P48, TET10.3
unnamed: AIN_N0T.49, AIN_N0T.P49, TET11.0
unnamed: AIN_N0T.50, AIN_N0T.P50, TET11.1
unnamed: AIN_N0T.51, AIN_N0T.P51, TET11.2
unnamed: AIN_N0T.52, AIN_N0T.P52, TET11.3
unnamed: AIN_N0T.53, AIN_N0T.P53, TET12.0
unnamed: AIN_N0T.54, AIN_N0T.P54, TET12.1
unnamed: AIN_N0T.55, AIN_N0T.P55, TET12.2
unnamed: AIN_N0T.56, AIN_N0T.P56, TET12.3
unnamed: AIN_N0T.57, AIN_N0T.P57, TET13.0
unnamed: AIN_N0T.58, AIN_N0T.P58, TET13.1
unnamed: AIN_N0T.59, AIN_N0T.P59, TET13.2
unnamed: AIN_N0T.60, AIN_N0T.P60, TET13.3
unnamed: AIN_N0T.61, AIN_N0T.P61, TET14.0
unnamed: AIN_N0T.62, AIN_N0T.P62, TET14.1
unnamed: AIN_N0T.63, AIN_N0T.P63, TET14.2
unnamed: AIN_N0T.64, AIN_N0T.P64, TET14.3
unnamed: AIN_N0T.65, TET15.0
unnamed: AIN_N0T.66, TET15.1
unnamed: AIN_N0T.67, TET15.2
unnamed: AIN_N0T.68, TET15.3
unnamed: SHLD_B2.P$1, SJ_B2.COM
unnamed: SHLD_B3.P$1, SJ_B3.COM
unnamed: AIN_N0T2.33, TET71.3
unnamed: AIN_N0T2.32, TET71.2
unnamed: AIN_N0T2.31, AIN_N0T2.P31, TET71.1
unnamed: AIN_N0T2.30, AIN_N0T2.P30, TET71.0
unnamed: AIN_N0T2.29, AIN_N0T2.P29, TET70.3
unnamed: AIN_N0T2.28, AIN_N0T2.P28, TET70.2
unnamed: AIN_N0T2.27, AIN_N0T2.P27, TET70.1
unnamed: AIN_N0T2.26, AIN_N0T2.P26, TET70.0
unnamed: AIN_N0T2.25, AIN_N0T2.P25, TET69.3
unnamed: AIN_N0T2.24, AIN_N0T2.P24, TET69.2
unnamed: AIN_N0T2.23, AIN_N0T2.P23, TET69.1
unnamed: AIN_N0T2.22, AIN_N0T2.P22, TET69.0
unnamed: AIN_N0T2.21, AIN_N0T2.P21, TET68.3
unnamed: AIN_N0T2.20, AIN_N0T2.P20, TET68.2
unnamed: AIN_N0T2.19, AIN_N0T2.P19, TET68.1
unnamed: AIN_N0T2.18, AIN_N0T2.P18, TET68.0
unnamed: AIN_N0T2.17, AIN_N0T2.P17, TET67.3
unnamed: AIN_N0T2.16, AIN_N0T2.P16, TET67.2
unnamed: AIN_N0T2.15, AIN_N0T2.P15, TET67.1
unnamed: AIN_N0T2.14, AIN_N0T2.P14, TET67.0
unnamed: AIN_N0T2.13, AIN_N0T2.P13, TET66.3
unnamed: AIN_N0T2.12, AIN_N0T2.P12, TET66.2
unnamed: AIN_N0T2.11, AIN_N0T2.P11, TET66.1
unnamed: AIN_N0T2.10, AIN_N0T2.P10, TET66.0
unnamed: AIN_N0T2.9, AIN_N0T2.P9, TET65.3
unnamed: AIN_N0T2.8, AIN_N0T2.P8, TET65.2
unnamed: AIN_N0T2.7, AIN_N0T2.P7, TET65.1
unnamed: AIN_N0T2.6, AIN_N0T2.P6, TET65.0
unnamed: AIN_N0T2.5, AIN_N0T2.P5, TET64.3
unnamed: AIN_N0T2.4, AIN_N0T2.P4, TET64.2
unnamed: AIN_N0T2.3, AIN_N0T2.P3, TET64.1
unnamed: AIN_N0T2.38, AIN_N0T2.P38, TET72.1
unnamed: AIN_N0T2.39, AIN_N0T2.P39, TET72.2
unnamed: AIN_N0T2.40, AIN_N0T2.P40, TET72.3
unnamed: AIN_N0T2.41, AIN_N0T2.P41, TET73.0
unnamed: AIN_N0T2.42, AIN_N0T2.P42, TET73.1
unnamed: AIN_N0T2.43, AIN_N0T2.P43, TET73.2
unnamed: AIN_N0T2.44, AIN_N0T2.P44, TET73.3
unnamed: AIN_N0T2.45, AIN_N0T2.P45, TET74.0
unnamed: AIN_N0T2.46, AIN_N0T2.P46, TET74.1
unnamed: AIN_N0T2.47, AIN_N0T2.P47, TET74.2
unnamed: AIN_N0T2.48, AIN_N0T2.P48, TET74.3
unnamed: AIN_N0T2.49, AIN_N0T2.P49, TET75.0
unnamed: AIN_N0T2.50, AIN_N0T2.P50, TET75.1
unnamed: AIN_N0T2.51, AIN_N0T2.P51, TET75.2
unnamed: AIN_N0T2.52, AIN_N0T2.P52, TET75.3
unnamed: AIN_N0T2.53, AIN_N0T2.P53, TET76.0
unnamed: AIN_N0T2.54, AIN_N0T2.P54, TET76.1
unnamed: AIN_N0T2.55, AIN_N0T2.P55, TET76.2
unnamed: AIN_N0T2.56, AIN_N0T2.P56, TET76.3
unnamed: AIN_N0T2.57, AIN_N0T2.P57, TET77.0
unnamed: AIN_N0T2.58, AIN_N0T2.P58, TET77.1
unnamed: AIN_N0T2.59, AIN_N0T2.P59, TET77.2
unnamed: AIN_N0T2.60, AIN_N0T2.P60, TET77.3
unnamed: AIN_N0T2.61, AIN_N0T2.P61, TET78.0
unnamed: AIN_N0T2.62, AIN_N0T2.P62, TET78.1
unnamed: AIN_N0T2.63, AIN_N0T2.P63, TET78.2
unnamed: AIN_N0T2.64, AIN_N0T2.P64, TET78.3
unnamed: AIN_N0T2.65, TET79.0
unnamed: AIN_N0T2.66, TET79.1
unnamed: AIN_N0T2.67, TET79.2
unnamed: AIN_N0T2.68, TET79.3
unnamed: AIN_N0T2.2, AIN_N0T2.P2, TET64.0
unnamed: AIN_N0T2.37, AIN_N0T2.P37, TET72.0
unnamed: AIN_S0T2.33, TET87.0
unnamed: AIN_S0T2.32, TET87.1
unnamed: AIN_S0T2.31, AIN_S0T2.P31, TET87.2
unnamed: AIN_S0T2.30, AIN_S0T2.P30, TET87.3
unnamed: AIN_S0T2.29, AIN_S0T2.P29, TET86.0
unnamed: AIN_S0T2.28, AIN_S0T2.P28, TET86.1
unnamed: AIN_S0T2.27, AIN_S0T2.P27, TET86.2
unnamed: AIN_S0T2.26, AIN_S0T2.P26, TET86.3
unnamed: AIN_S0T2.25, AIN_S0T2.P25, TET85.0
unnamed: AIN_S0T2.24, AIN_S0T2.P24, TET85.1
unnamed: AIN_S0T2.23, AIN_S0T2.P23, TET85.2
unnamed: AIN_S0T2.22, AIN_S0T2.P22, TET85.3
unnamed: AIN_S0T2.21, AIN_S0T2.P21, TET84.0
unnamed: AIN_S0T2.20, AIN_S0T2.P20, TET84.1
unnamed: AIN_S0T2.19, AIN_S0T2.P19, TET84.2
unnamed: AIN_S0T2.18, AIN_S0T2.P18, TET84.3
unnamed: AIN_S0T2.17, AIN_S0T2.P17, TET83.0
unnamed: AIN_S0T2.16, AIN_S0T2.P16, TET83.1
unnamed: AIN_S0T2.15, AIN_S0T2.P15, TET83.2
unnamed: AIN_S0T2.14, AIN_S0T2.P14, TET83.3
unnamed: AIN_S0T2.13, AIN_S0T2.P13, TET82.0
unnamed: AIN_S0T2.12, AIN_S0T2.P12, TET82.1
unnamed: AIN_S0T2.11, AIN_S0T2.P11, TET82.2
unnamed: AIN_S0T2.10, AIN_S0T2.P10, TET82.3
unnamed: AIN_S0T2.9, AIN_S0T2.P9, TET81.0
unnamed: AIN_S0T2.8, AIN_S0T2.P8, TET81.1
unnamed: AIN_S0T2.7, AIN_S0T2.P7, TET81.2
unnamed: AIN_S0T2.6, AIN_S0T2.P6, TET81.3
unnamed: AIN_S0T2.5, AIN_S0T2.P5, TET80.0
unnamed: AIN_S0T2.4, AIN_S0T2.P4, TET80.1
unnamed: AIN_S0T2.3, AIN_S0T2.P3, TET80.2
unnamed: AIN_S0T2.38, AIN_S0T2.P38, TET88.2
unnamed: AIN_S0T2.39, AIN_S0T2.P39, TET88.1
unnamed: AIN_S0T2.40, AIN_S0T2.P40, TET88.0
unnamed: AIN_S0T2.41, AIN_S0T2.P41, TET89.3
unnamed: AIN_S0T2.42, AIN_S0T2.P42, TET89.2
unnamed: AIN_S0T2.43, AIN_S0T2.P43, TET89.1
unnamed: AIN_S0T2.44, AIN_S0T2.P44, TET89.0
unnamed: AIN_S0T2.45, AIN_S0T2.P45, TET90.3
unnamed: AIN_S0T2.46, AIN_S0T2.P46, TET90.2
unnamed: AIN_S0T2.47, AIN_S0T2.P47, TET90.1
unnamed: AIN_S0T2.48, AIN_S0T2.P48, TET90.0
unnamed: AIN_S0T2.49, AIN_S0T2.P49, TET91.3
unnamed: AIN_S0T2.50, AIN_S0T2.P50, TET91.2
unnamed: AIN_S0T2.51, AIN_S0T2.P51, TET91.1
unnamed: AIN_S0T2.52, AIN_S0T2.P52, TET91.0
unnamed: AIN_S0T2.53, AIN_S0T2.P53, TET92.3
unnamed: AIN_S0T2.54, AIN_S0T2.P54, TET92.2
unnamed: AIN_S0T2.55, AIN_S0T2.P55, TET92.1
unnamed: AIN_S0T2.56, AIN_S0T2.P56, TET92.0
unnamed: AIN_S0T2.57, AIN_S0T2.P57, TET93.3
unnamed: AIN_S0T2.58, AIN_S0T2.P58, TET93.2
unnamed: AIN_S0T2.59, AIN_S0T2.P59, TET93.1
unnamed: AIN_S0T2.60, AIN_S0T2.P60, TET93.0
unnamed: AIN_S0T2.61, AIN_S0T2.P61, TET94.3
unnamed: AIN_S0T2.62, AIN_S0T2.P62, TET94.2
unnamed: AIN_S0T2.63, AIN_S0T2.P63, TET94.1
unnamed: AIN_S0T2.64, AIN_S0T2.P64, TET94.0
unnamed: AIN_S0T2.65, TET95.3
unnamed: AIN_S0T2.66, TET95.2
unnamed: AIN_S0T2.67, TET95.1
unnamed: AIN_S0T2.68, TET95.0
unnamed: AIN_S0T2.2, AIN_S0T2.P2, TET80.3
unnamed: AIN_S0T2.37, AIN_S0T2.P37, TET88.3
unnamed: SHLD_A4.P$1, SJ_A4.COM
unnamed: SHLD_A5.P$1, SJ_A5.COM
unnamed: SHLD_B4.P$1, SJ_B4.COM
unnamed: SHLD_B5.P$1, SJ_B5.COM
unnamed: AIN_N0T3.33, TET103.3
unnamed: AIN_N0T3.32, TET103.2
unnamed: AIN_N0T3.31, AIN_N0T3.P31, TET103.1
unnamed: AIN_N0T3.30, AIN_N0T3.P30, TET103.0
unnamed: AIN_N0T3.29, AIN_N0T3.P29, TET102.3
unnamed: AIN_N0T3.28, AIN_N0T3.P28, TET102.2
unnamed: AIN_N0T3.27, AIN_N0T3.P27, TET102.1
unnamed: AIN_N0T3.26, AIN_N0T3.P26, TET102.0
unnamed: AIN_N0T3.25, AIN_N0T3.P25, TET101.3
unnamed: AIN_N0T3.24, AIN_N0T3.P24, TET101.2
unnamed: AIN_N0T3.23, AIN_N0T3.P23, TET101.1
unnamed: AIN_N0T3.22, AIN_N0T3.P22, TET101.0
unnamed: AIN_N0T3.21, AIN_N0T3.P21, TET100.3
unnamed: AIN_N0T3.20, AIN_N0T3.P20, TET100.2
unnamed: AIN_N0T3.19, AIN_N0T3.P19, TET100.1
unnamed: AIN_N0T3.18, AIN_N0T3.P18, TET100.0
unnamed: AIN_N0T3.17, AIN_N0T3.P17, TET99.3
unnamed: AIN_N0T3.16, AIN_N0T3.P16, TET99.2
unnamed: AIN_N0T3.15, AIN_N0T3.P15, TET99.1
unnamed: AIN_N0T3.14, AIN_N0T3.P14, TET99.0
unnamed: AIN_N0T3.13, AIN_N0T3.P13, TET98.3
unnamed: AIN_N0T3.12, AIN_N0T3.P12, TET98.2
unnamed: AIN_N0T3.11, AIN_N0T3.P11, TET98.1
unnamed: AIN_N0T3.10, AIN_N0T3.P10, TET98.0
unnamed: AIN_N0T3.9, AIN_N0T3.P9, TET97.3
unnamed: AIN_N0T3.8, AIN_N0T3.P8, TET97.2
unnamed: AIN_N0T3.7, AIN_N0T3.P7, TET97.1
unnamed: AIN_N0T3.6, AIN_N0T3.P6, TET97.0
unnamed: AIN_N0T3.5, AIN_N0T3.P5, TET96.3
unnamed: AIN_N0T3.4, AIN_N0T3.P4, TET96.2
unnamed: AIN_N0T3.3, AIN_N0T3.P3, TET96.1
unnamed: AIN_N0T3.38, AIN_N0T3.P38, TET104.1
unnamed: AIN_N0T3.39, AIN_N0T3.P39, TET104.2
unnamed: AIN_N0T3.40, AIN_N0T3.P40, TET104.3
unnamed: AIN_N0T3.41, AIN_N0T3.P41, TET105.0
unnamed: AIN_N0T3.42, AIN_N0T3.P42, TET105.1
unnamed: AIN_N0T3.43, AIN_N0T3.P43, TET105.2
unnamed: AIN_N0T3.44, AIN_N0T3.P44, TET105.3
unnamed: AIN_N0T3.45, AIN_N0T3.P45, TET106.0
unnamed: AIN_N0T3.46, AIN_N0T3.P46, TET106.1
unnamed: AIN_N0T3.47, AIN_N0T3.P47, TET106.2
unnamed: AIN_N0T3.48, AIN_N0T3.P48, TET106.3
unnamed: AIN_N0T3.49, AIN_N0T3.P49, TET107.0
unnamed: AIN_N0T3.50, AIN_N0T3.P50, TET107.1
unnamed: AIN_N0T3.51, AIN_N0T3.P51, TET107.2
unnamed: AIN_N0T3.52, AIN_N0T3.P52, TET107.3
unnamed: AIN_N0T3.53, AIN_N0T3.P53, TET108.0
unnamed: AIN_N0T3.54, AIN_N0T3.P54, TET108.1
unnamed: AIN_N0T3.55, AIN_N0T3.P55, TET108.2
unnamed: AIN_N0T3.56, AIN_N0T3.P56, TET108.3
unnamed: AIN_N0T3.57, AIN_N0T3.P57, TET109.0
unnamed: AIN_N0T3.58, AIN_N0T3.P58, TET109.1
unnamed: AIN_N0T3.59, AIN_N0T3.P59, TET109.2
unnamed: AIN_N0T3.60, AIN_N0T3.P60, TET109.3
unnamed: AIN_N0T3.61, AIN_N0T3.P61, TET110.0
unnamed: AIN_N0T3.62, AIN_N0T3.P62, TET110.1
unnamed: AIN_N0T3.63, AIN_N0T3.P63, TET110.2
unnamed: AIN_N0T3.64, AIN_N0T3.P64, TET110.3
unnamed: AIN_N0T3.65, TET111.0
unnamed: AIN_N0T3.66, TET111.1
unnamed: AIN_N0T3.67, TET111.2
unnamed: AIN_N0T3.68, TET111.3
unnamed: AIN_N0T3.2, AIN_N0T3.P2, TET96.0
unnamed: AIN_N0T3.37, AIN_N0T3.P37, TET104.0
unnamed: AIN_S0T3.33, TET119.0
unnamed: AIN_S0T3.32, TET119.1
unnamed: AIN_S0T3.31, AIN_S0T3.P31, TET119.2
unnamed: AIN_S0T3.30, AIN_S0T3.P30, TET119.3
unnamed: AIN_S0T3.29, AIN_S0T3.P29, TET118.0
unnamed: AIN_S0T3.28, AIN_S0T3.P28, TET118.1
unnamed: AIN_S0T3.27, AIN_S0T3.P27, TET118.2
unnamed: AIN_S0T3.26, AIN_S0T3.P26, TET118.3
unnamed: AIN_S0T3.25, AIN_S0T3.P25, TET117.0
unnamed: AIN_S0T3.24, AIN_S0T3.P24, TET117.1
unnamed: AIN_S0T3.23, AIN_S0T3.P23, TET117.2
unnamed: AIN_S0T3.22, AIN_S0T3.P22, TET117.3
unnamed: AIN_S0T3.21, AIN_S0T3.P21, TET116.0
unnamed: AIN_S0T3.20, AIN_S0T3.P20, TET116.1
unnamed: AIN_S0T3.19, AIN_S0T3.P19, TET116.2
unnamed: AIN_S0T3.18, AIN_S0T3.P18, TET116.3
unnamed: AIN_S0T3.17, AIN_S0T3.P17, TET115.0
unnamed: AIN_S0T3.16, AIN_S0T3.P16, TET115.1
unnamed: AIN_S0T3.15, AIN_S0T3.P15, TET115.2
unnamed: AIN_S0T3.14, AIN_S0T3.P14, TET115.3
unnamed: AIN_S0T3.13, AIN_S0T3.P13, TET114.0
unnamed: AIN_S0T3.12, AIN_S0T3.P12, TET114.1
unnamed: AIN_S0T3.11, AIN_S0T3.P11, TET114.2
unnamed: AIN_S0T3.10, AIN_S0T3.P10, TET114.3
unnamed: AIN_S0T3.9, AIN_S0T3.P9, TET113.0
unnamed: AIN_S0T3.8, AIN_S0T3.P8, TET113.1
unnamed: AIN_S0T3.7, AIN_S0T3.P7, TET113.2
unnamed: AIN_S0T3.6, AIN_S0T3.P6, TET113.3
unnamed: AIN_S0T3.5, AIN_S0T3.P5, TET112.0
unnamed: AIN_S0T3.4, AIN_S0T3.P4, TET112.1
unnamed: AIN_S0T3.3, AIN_S0T3.P3, TET112.2
unnamed: AIN_S0T3.38, AIN_S0T3.P38, TET120.2
unnamed: AIN_S0T3.39, AIN_S0T3.P39, TET120.1
unnamed: AIN_S0T3.40, AIN_S0T3.P40, TET120.0
unnamed: AIN_S0T3.41, AIN_S0T3.P41, TET121.3
unnamed: AIN_S0T3.42, AIN_S0T3.P42, TET121.2
unnamed: AIN_S0T3.43, AIN_S0T3.P43, TET121.1
unnamed: AIN_S0T3.44, AIN_S0T3.P44, TET121.0
unnamed: AIN_S0T3.45, AIN_S0T3.P45, TET122.3
unnamed: AIN_S0T3.46, AIN_S0T3.P46, TET122.2
unnamed: AIN_S0T3.47, AIN_S0T3.P47, TET122.1
unnamed: AIN_S0T3.48, AIN_S0T3.P48, TET122.0
unnamed: AIN_S0T3.49, AIN_S0T3.P49, TET123.3
unnamed: AIN_S0T3.50, AIN_S0T3.P50, TET123.2
unnamed: AIN_S0T3.51, AIN_S0T3.P51, TET123.1
unnamed: AIN_S0T3.52, AIN_S0T3.P52, TET123.0
unnamed: AIN_S0T3.53, AIN_S0T3.P53, TET124.3
unnamed: AIN_S0T3.54, AIN_S0T3.P54, TET124.2
unnamed: AIN_S0T3.55, AIN_S0T3.P55, TET124.1
unnamed: AIN_S0T3.56, AIN_S0T3.P56, TET124.0
unnamed: AIN_S0T3.57, AIN_S0T3.P57, TET125.3
unnamed: AIN_S0T3.58, AIN_S0T3.P58, TET125.2
unnamed: AIN_S0T3.59, AIN_S0T3.P59, TET125.1
unnamed: AIN_S0T3.60, AIN_S0T3.P60, TET125.0
unnamed: AIN_S0T3.61, AIN_S0T3.P61, TET126.3
unnamed: AIN_S0T3.62, AIN_S0T3.P62, TET126.2
unnamed: AIN_S0T3.63, AIN_S0T3.P63, TET126.1
unnamed: AIN_S0T3.64, AIN_S0T3.P64, TET126.0
unnamed: AIN_S0T3.65, TET127.3
unnamed: AIN_S0T3.66, TET127.2
unnamed: AIN_S0T3.67, TET127.1
unnamed: AIN_S0T3.68, TET127.0
unnamed: AIN_S0T3.2, AIN_S0T3.P2, TET112.3
unnamed: AIN_S0T3.37, AIN_S0T3.P37, TET120.3
unnamed: SHLD_A6.P$1, SJ_A6.COM
unnamed: SHLD_A7.P$1, SJ_A7.COM
unnamed: SHLD_B6.P$1, SJ_B6.COM
unnamed: SHLD_B7.P$1, SJ_B7.COM
unnamed: AIN_N0T4.33, TET135.3
unnamed: AIN_N0T4.32, TET135.2
unnamed: AIN_N0T4.31, AIN_N0T4.P31, TET135.1
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

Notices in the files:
2x64_Hirose_Circular/README.md:
128 Channel Circular
Hirose Headstage Module by Jonathan P. Newman is licensed under a Creative
Common
2x64_Hirose_Circular/eib/eib-128_panel.brd:
CC BY-SA-NC-4.0
2x64_Hirose_Circular/spi-interface/single-spi-interface.sch:
LICENSE: (c) Jon Newman CC-BY-SA-NC 4.0
